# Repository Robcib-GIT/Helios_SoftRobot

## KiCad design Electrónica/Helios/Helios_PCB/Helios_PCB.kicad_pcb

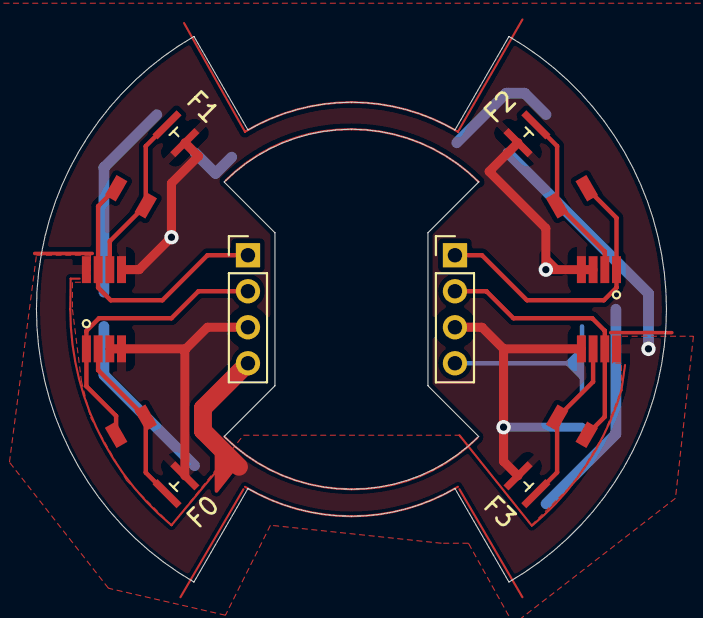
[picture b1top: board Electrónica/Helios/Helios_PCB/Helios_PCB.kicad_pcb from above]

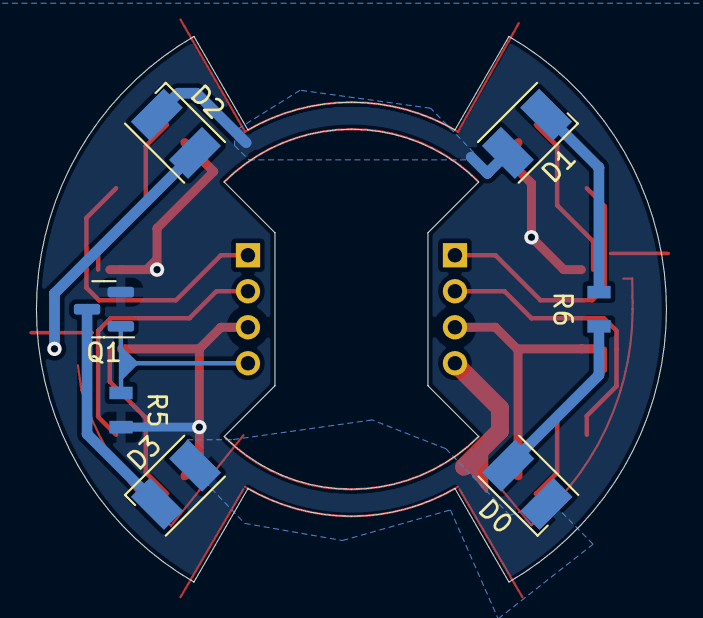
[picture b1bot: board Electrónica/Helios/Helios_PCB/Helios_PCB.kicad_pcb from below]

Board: 2 copper layers, 35.0 x 30.3 mm, 19 parts (7 on the bottom side), 16 nets.

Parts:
D0, D1, D2, D3: LED; LED_PLCC-2
F0, F1, F2, F3: SFH2704; SFH2704_Photodiode
J0: Connector J0; PinHeader_1x04_P2.00mm_Vertical
J1: Connector J1; PinHeader_1x04_P2.00mm_Vertical
Q1: AO3400A; SOT-23
R0, R1, R2, R3, R5, R6: R; RS_0805
U0, U1: OPA2380

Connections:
GND: F0.2 (A), F1.2 (A), F2.2 (A), F3.2 (A), J0.3, J1.3, Q1.2 (S), R5.2, U0.3 (+IA), U0.4 (GND), U0.5 (+IB), U1.3 (+IA), U1.4 (GND), U1.5 (+IB)
LED: J1.4, Q1.1 (G), R5.1
unnamed: D0.1 (K), D3.2 (A)
unnamed: D1.1 (K), R6.2
unnamed: D1.2 (A), D2.1 (K)
unnamed: D3.1 (K), Q1.3 (D)
unnamed: F0.1 (K), R0.2, U0.2 (-IA)
unnamed: F1.1 (K), R1.2, U0.6 (-IB)
unnamed: F2.1 (K), R2.2, U1.2 (-IA)
unnamed: F3.1 (K), R3.2, U1.6 (-IB)
unnamed: D0.2 (A), R6.1
O0: J0.1, R1.1, U0.7 (OB)
O1: J0.2, R0.1, U0.1 (OA)
O2: J1.1, R2.1, U1.1 (OA)
O3: J1.2, R3.1, U1.7 (OB)
VCC: D2.2 (A), J0.4, U0.8 (VCC), U1.8 (VCC)

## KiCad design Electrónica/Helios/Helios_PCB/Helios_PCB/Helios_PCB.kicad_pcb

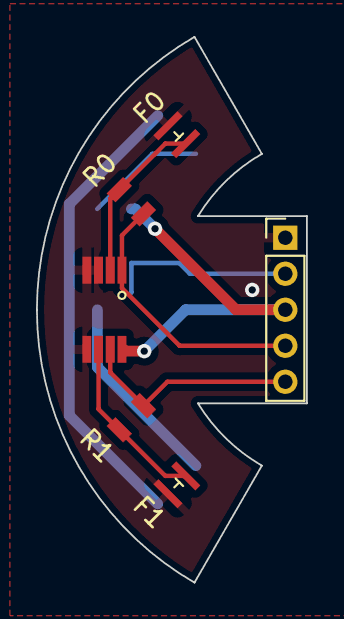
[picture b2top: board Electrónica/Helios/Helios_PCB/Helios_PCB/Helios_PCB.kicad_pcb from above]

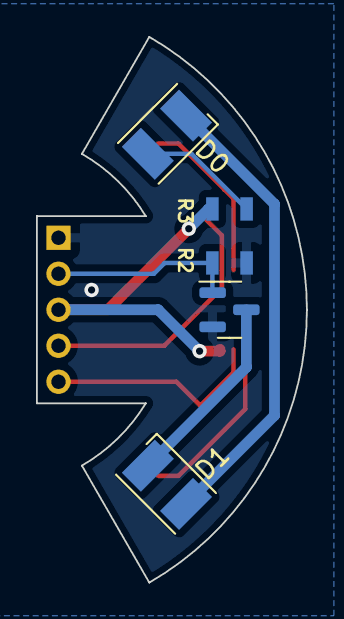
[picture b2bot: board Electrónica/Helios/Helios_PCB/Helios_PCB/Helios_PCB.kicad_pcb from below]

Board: 2 copper layers, 15.0 x 30.3 mm, 11 parts (5 on the bottom side), 10 nets.

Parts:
D0, D1: LED; LED_PLCC-2
F0, F1: SFH2704; SFH2704_Photodiode
J0: Conn_01x05_Male; PinHeader_1x05_P2.00mm_Vertical
Q0: AO3400A; SOT-23
R0, R1: Rf; RS_0805
R2: RL; RS_0805
R3: Rpd; RS_0805
U0: OPA2380

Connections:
GND: F0.2 (A), F1.2 (A), J0.1, Q0.2 (S), R3.2, U0.3 (+IA), U0.4 (GND), U0.5 (+IB)
LED: J0.2, Q0.1 (G), R3.1
unnamed: D0.1 (K), D1.2 (A)
unnamed: D1.1 (K), Q0.3 (D)
unnamed: F0.1 (K), R0.2, U0.2 (-IA)
unnamed: F1.1 (K), R1.2, U0.6 (-IB)
unnamed: D0.2 (A), R2.1
O0: J0.4, R0.1, U0.1 (OA)
O1: J0.5, R1.1, U0.7 (OB)
VCC: J0.3, R2.2, U0.8 (VCC)

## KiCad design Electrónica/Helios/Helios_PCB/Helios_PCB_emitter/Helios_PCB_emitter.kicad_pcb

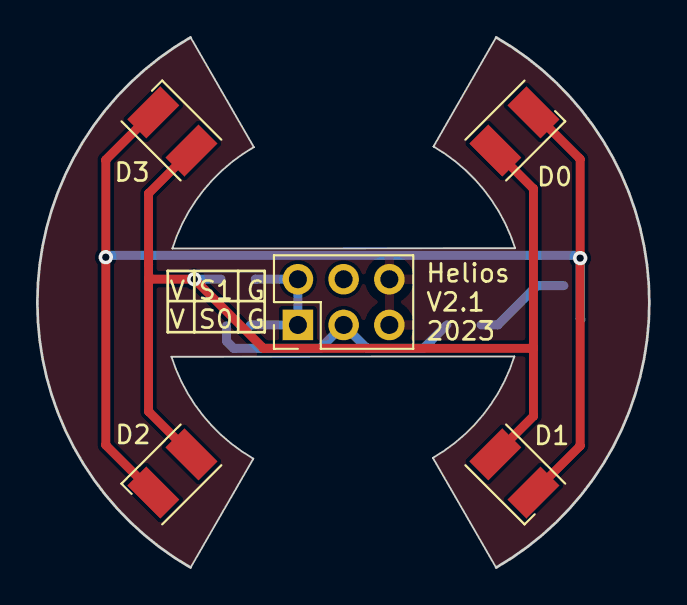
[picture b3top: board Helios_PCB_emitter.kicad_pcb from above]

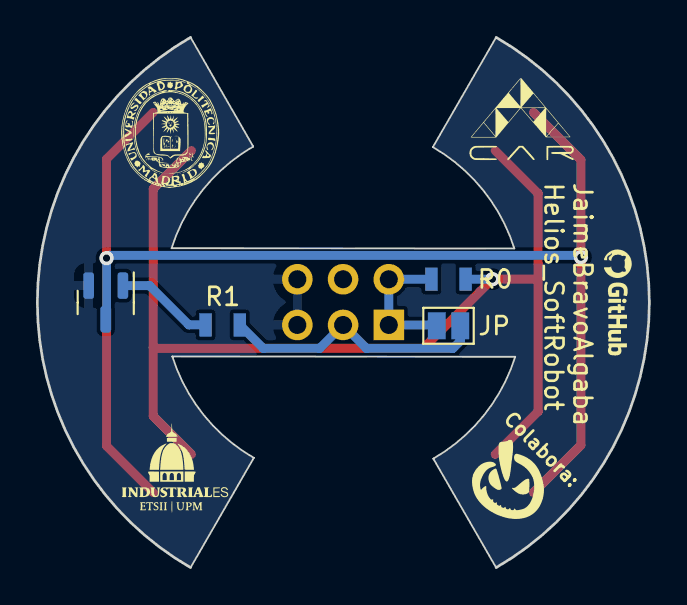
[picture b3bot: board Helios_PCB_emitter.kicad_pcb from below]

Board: 2 copper layers, 34.0 x 29.5 mm, 9 parts (4 on the bottom side), 6 nets.

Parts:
D0, D1, D2, D3: LED; LED_PLCC-2
J1: Conn_02x03_Counter_Clockwise; PinHeader_2x03_P2.54mm_Vertical
JP: SolderJumper_2_Open; SolderJumper-2_P1.3mm_Open_Pad1.0x1.5mm
Q1: MMBT3904; SOT-23
R0: RL; RS_0805
R1: Rpd; RS_0805

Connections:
GND: J1.5, J1.6, Q1.2 (E)
unnamed: D0.2 (A), D1.2 (A), D2.2 (A), D3.2 (A), R0.1
unnamed: D0.1 (K), D1.1 (K), D2.1 (K), D3.1 (K), Q1.3 (C)
unnamed: Q1.1 (B), R1.2
S0: J1.3, JP.2 (B), R1.1
VCC: J1.1, J1.2, JP.1 (A), R0.2

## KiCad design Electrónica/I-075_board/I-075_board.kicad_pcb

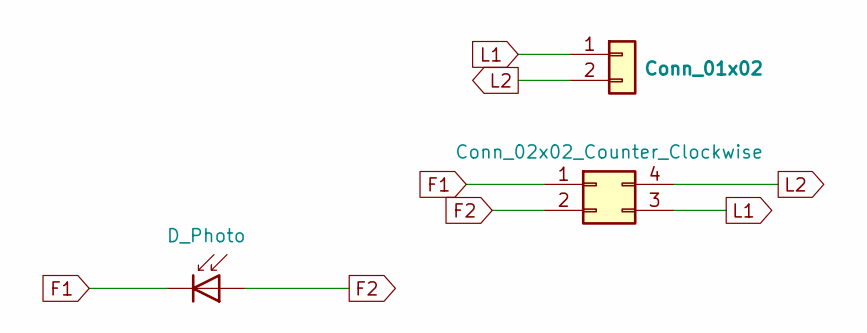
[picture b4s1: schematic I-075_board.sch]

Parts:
D1: D_Photo; SFH2704
J1: Conn_02x02_Counter_Clockwise; I-075
J2: Conn_01x02; I-075_wires

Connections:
F1: D1.1 (K), J1.1
F2: D1.2 (A), J1.2
L1: J1.3, J2.1
L2: J1.4, J2.2

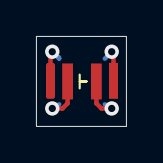
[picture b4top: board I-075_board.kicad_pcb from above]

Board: 2 copper layers, 5.0 x 5.0 mm, 3 parts (1 on the bottom side), 4 nets.
